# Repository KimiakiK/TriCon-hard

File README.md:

# TriCon
[Software](https://github.com/KimiakiK/TriCon-soft)

# Features
- 3つのコントローラーが繋がる小型携帯ゲーム機

# Major Components  
- STM32F303K8
- 0.96インチ 128×64ドット有機ELディスプレイ
- ボタン電池 CR2032

# Photos

## PCB
- V1.1

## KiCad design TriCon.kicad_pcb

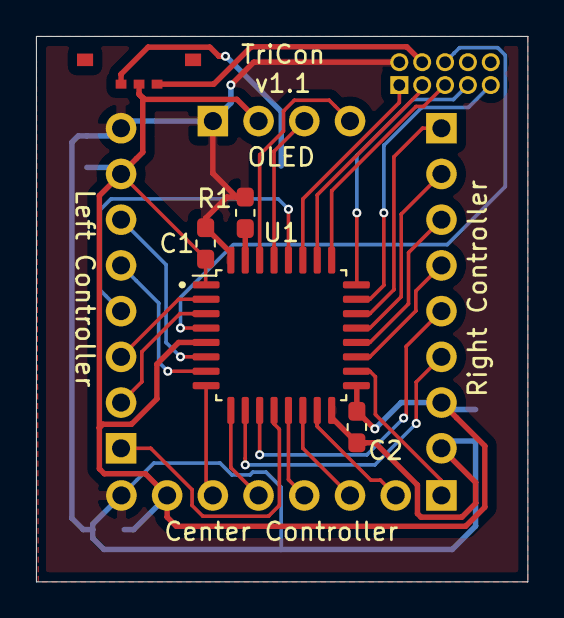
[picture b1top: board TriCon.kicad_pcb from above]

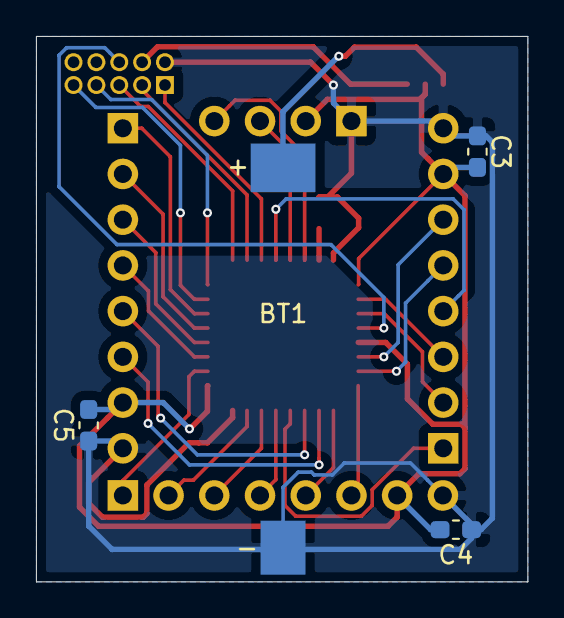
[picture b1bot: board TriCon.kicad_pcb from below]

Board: 2 copper layers, 27.3 x 30.3 mm, 14 parts (4 on the bottom side), 31 nets.

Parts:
BT1: CR2032; CR2032_SMD
C1, C2, C3, C4, C5: 0.1uF; C_0603_1608Metric_Pad1.05x0.95mm_HandSolder
Center Controller: Controller Center; PinHeader_1x08_P2.54mm_Vertical
J1: STM32 Debug; PinHeader_2x05_P1.27mm_Vertical
Left Controller: Controller Left; PinHeader_1x08_P2.54mm_Vertical
OLED: OLED128x64; PinHeader_1x04_P2.54mm_Vertical
R1: 10k; R_0603_1608Metric_Pad1.05x0.95mm_HandSolder
Right Controller: Controller Right; PinHeader_1x08_P2.54mm_Vertical
SW1: SW_SPDT; Switch_SSAJ120100
U1: STM32F303K8T6; LQFP-32_7x7mm_P0.8mm

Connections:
+3V0: C1.1, C2.1, C3.1, C4.1, C5.1, Center Controller.7, Left Controller.7, OLED.2, Right Controller.7, SW1.2, U1.1, U1.5, U1.17
GND: BT1.2, C1.2, C2.2, C3.2, C4.2, C5.2, Center Controller.8, J1.2, Left Controller.8, OLED.1, R1.2, Right Controller.8, U1.16, U1.32
NRST: J1.6, U1.4
unnamed: BT1.1, SW1.3
unnamed: J1.1, U1.27
unnamed: J1.3, U1.26
unnamed: J1.4, SW1.1
unnamed: J1.5, U1.25
unnamed: J1.7, U1.24
unnamed: J1.9, U1.23
unnamed: OLED.3, U1.29
unnamed: OLED.4, U1.30
unnamed: Left Controller.1, U1.12
unnamed: Left Controller.2, U1.3
unnamed: Left Controller.3, U1.2
unnamed: Left Controller.4, U1.28
unnamed: Left Controller.5, U1.7
unnamed: Left Controller.6, U1.6
unnamed: Right Controller.1, U1.22
unnamed: Right Controller.2, U1.21
unnamed: Right Controller.3, U1.20
unnamed: Right Controller.4, U1.19
unnamed: Right Controller.5, U1.11
unnamed: Right Controller.6, U1.10
unnamed: Center Controller.1, U1.18
unnamed: Center Controller.2, U1.15
unnamed: Center Controller.3, U1.14
unnamed: Center Controller.4, U1.13
unnamed: Center Controller.5, U1.9
unnamed: Center Controller.6, U1.8
unnamed: R1.1, U1.31

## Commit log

2021-02-10 基板 V1.0
2021-02-10 基板 V1.1
2021-04-29 Add images
